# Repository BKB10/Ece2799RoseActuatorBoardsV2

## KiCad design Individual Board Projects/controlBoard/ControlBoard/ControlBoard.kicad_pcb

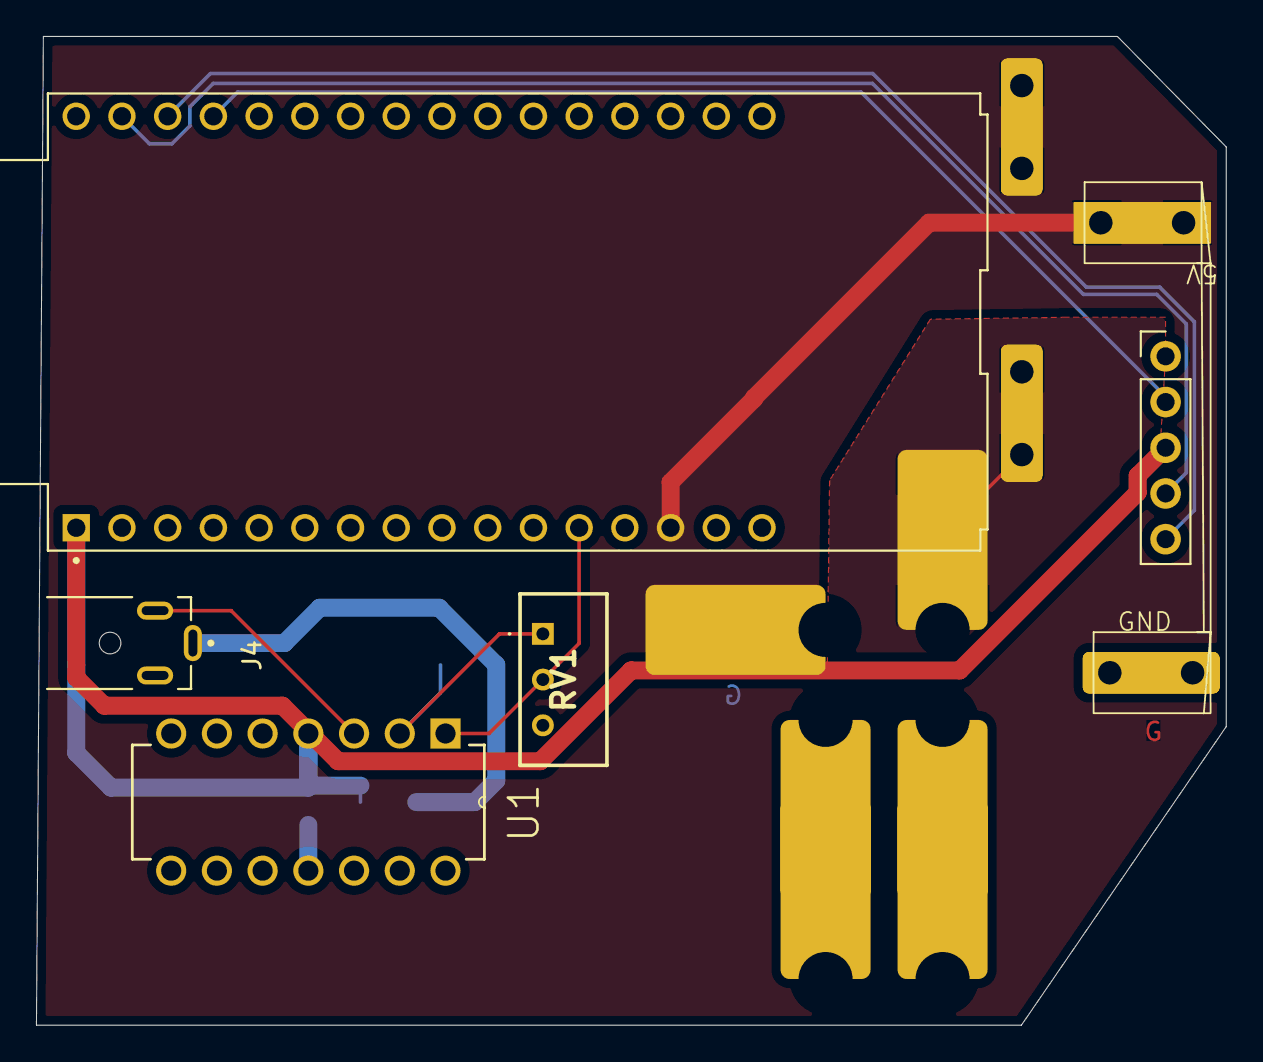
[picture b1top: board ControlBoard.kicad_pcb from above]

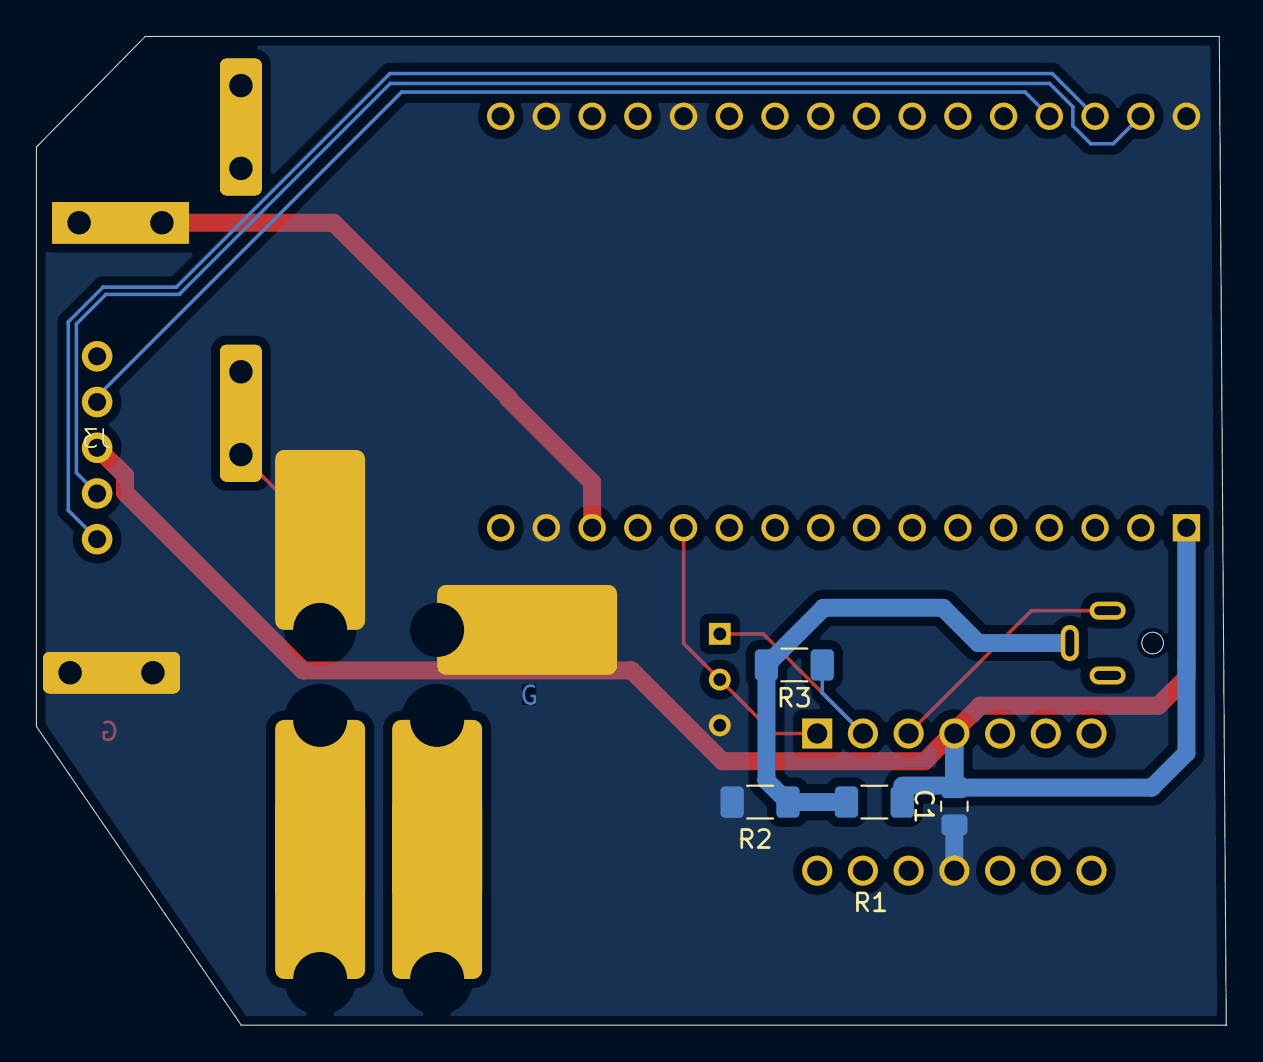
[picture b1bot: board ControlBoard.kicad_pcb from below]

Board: 2 copper layers, 66.1 x 54.9 mm, 12 parts (4 on the bottom side), 13 nets.

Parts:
B1: 12-24V -> 5V 20A; Buck-fourpins
C1: .1u; C_0805_2012Metric_Pad1.18x1.45mm_HandSolder
J1: USBCPD; USBC-PD-Module-twopins
J3: 5x2.54mm+2xBus; InterModuleConnectorMside
J4: MJ1-2503A; SAMESKY_MJ1-2503A
R1, R2: 40k; R_1206_3216Metric_Pad1.30x1.75mm_HandSolder
R3: 50; R_1206_3216Metric_Pad1.30x1.75mm_HandSolder
RV1: 1-400k; Potentiometer
U1: LMC6484IN_NOPB; DIP254P762X508-14
U2: 01000020Z
U3: ESP32-C6-DEVKITC-1-N8; MODULE_ESP32-C6-DEVKITC-1-N8

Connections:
+1.65V: J4.1, R1.2, R2.1, R3.2
+3.3V: C1.2, J3.4, R1.1, U1.4 (V+), U3.J1_1 (ESP_3V3)
+5V: J3.1, U2.2, U3.J1_14 (VCC_5V)
/ESP32_UART_RX: J3.6, U3.J3_3 (UART_RXD)
/ESP32_UART_TX: J3.5, U3.J3_2 (UART_TXD)
/To ESP32 ADC: RV1.2, U1.1 (OUT1), U3.J1_12 (GPIO2)
/USBC+: B1.1 (+Vin), J1.1
/USBC-: B1.2 (-Vin), J1.2
/nShoutRecive: J3.3, U3.J3_4 (GPIO15)
GND: B1.4 (-Vout), C1.1, J3.7, R2.2, RV1.3, U1.11 (V-), U3.J1_15 (GND_J1_15), U3.J3_1 (GND_J3_1), U3.J3_12 (GND_J3_12), U3.J3_15 (GND_J3_15)
unnamed: B1.3 (+Vout), U2.1
unnamed: R3.1, RV1.1, U1.2 (NEG1)
unnamed: J4.3, U1.3 (POS1)

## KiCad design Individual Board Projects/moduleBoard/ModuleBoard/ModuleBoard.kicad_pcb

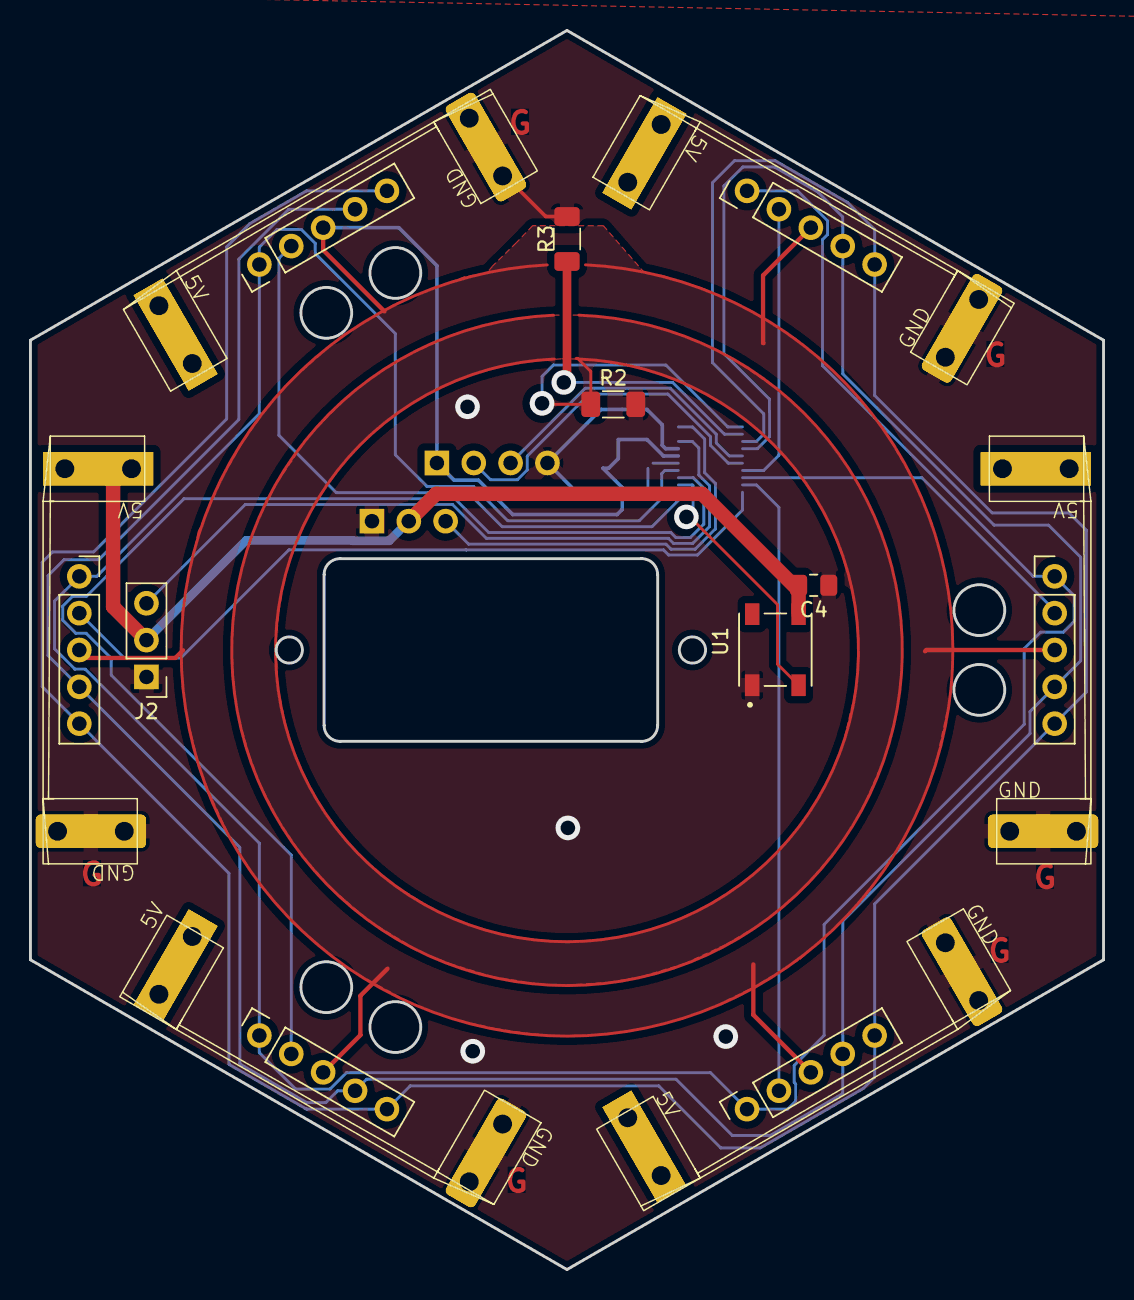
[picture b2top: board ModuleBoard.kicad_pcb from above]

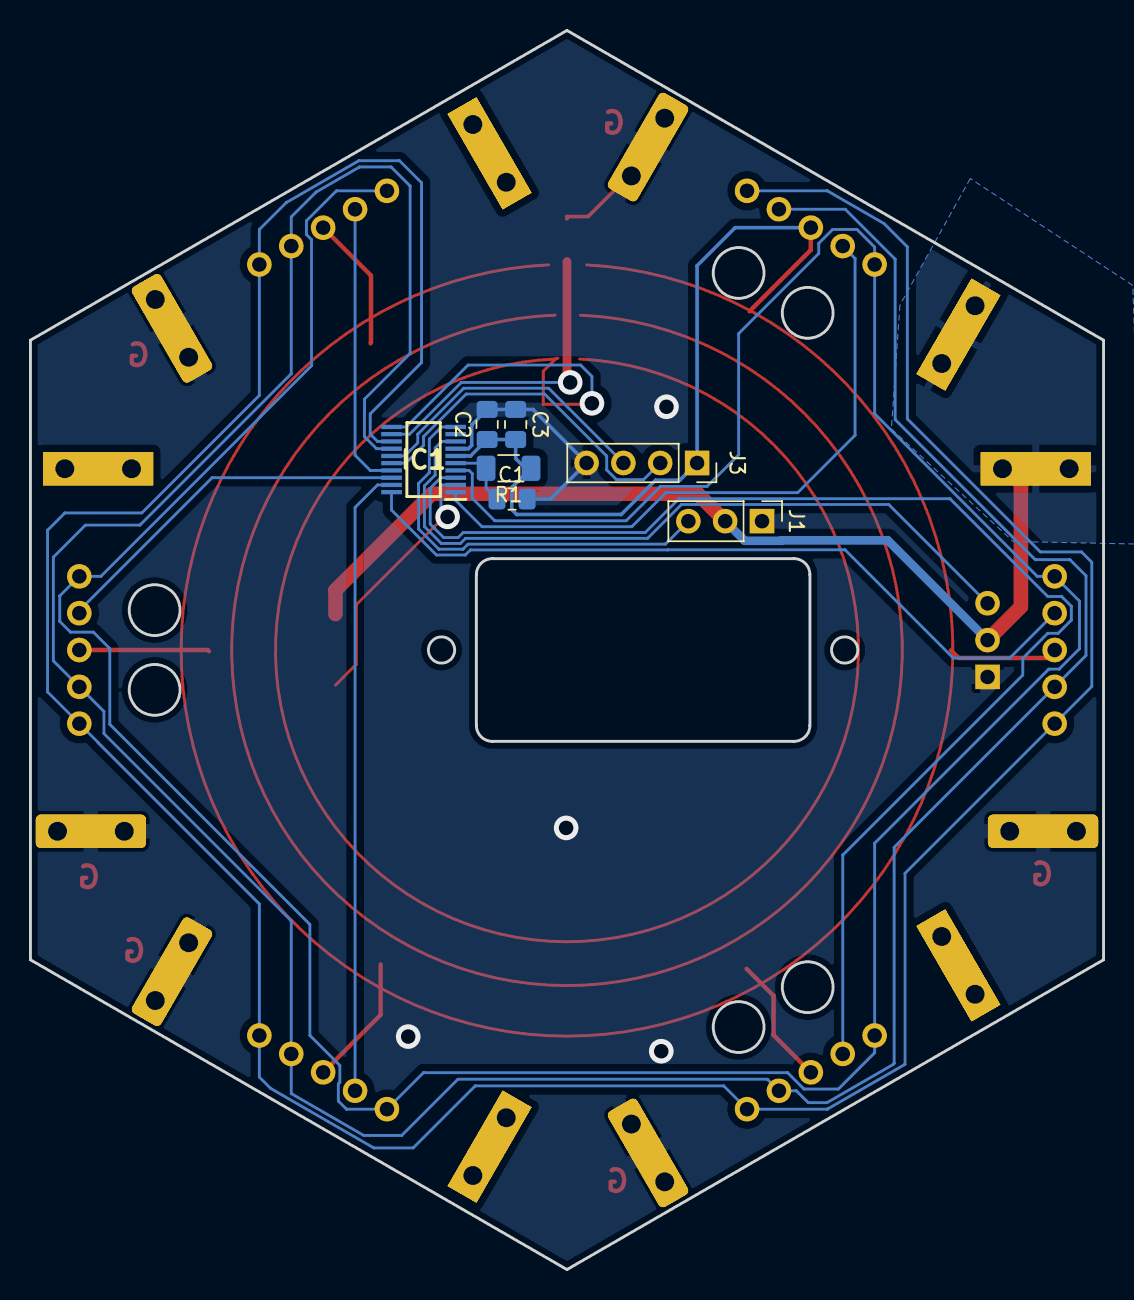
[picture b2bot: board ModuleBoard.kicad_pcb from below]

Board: 2 copper layers, 74.0 x 85.4 mm, 18 parts (7 on the bottom side), 20 nets.

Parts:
C1: 10n; C_0805_2012Metric_Pad1.18x1.45mm_HandSolder
C2: 10u; C_0805_2012Metric_Pad1.18x1.45mm_HandSolder
C3, C4: .1u; C_0805_2012Metric_Pad1.18x1.45mm_HandSolder
IC1: MSPM0C1103SDGS20R
J1: Rotation Servo; PinHeader_1x03_P2.54mm_Vertical
J2: Extention Servo; PinHeader_1x03_P2.54mm_Vertical
J3: Debug; PinSocket_1x04_P2.54mm_Vertical
J4, J5, J6, J7, J8, J9: 5x2.54mm+2xBus; InterModuleConnectorMside
R1: 47k; R_1206_3216Metric_Pad1.30x1.75mm_HandSolder
R2, R3: 40k; R_1206_3216Metric_Pad1.30x1.75mm_HandSolder
U1: FZ2812-5050; LED_FZ2812-5050

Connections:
+3.3V: C2.1, C3.2, IC1.6 (VDD), J3.1, J4.4, J5.4, J6.4, J7.4, J8.4, J9.4, R1.1
+5V: C4.2, J1.2, J2.2, J4.1, J5.1, J6.1, J7.1, J8.1, J9.1, U1.3 (VDD)
/Extention Bottom Out: IC1.11 (PA11), R2.1
/LED Sig: IC1.2 (PA27_/_A0), U1.2 (DIN)
/Linear Motor PWM: IC1.8 (PA2), J2.3
/MSP RX: IC1.14 (PA18_/_A7), J4.5, J5.5, J6.5, J7.5, J8.5, J9.5
/MSP TX: IC1.13 (PA17), J4.6, J5.6, J6.6, J7.6, J8.6, J9.6
/Rotary Motor PWM: IC1.10 (PA6), J1.3
/Rotation Key: IC1.12 (PA16_/_A8), R3.1
/SWCLK: IC1.16 (PA20_/_A6_/_SWCLK), J3.2
/SWDIO: IC1.15 (PA19_/_SWDIO), J3.3
/nShoutIn1: IC1.3 (PA28_/_A5), J4.3
/nShoutIn2: IC1.17 (PA22_/_A4), J7.3
/nShoutIn3: IC1.19 (PA24_/_A3), J5.3
/nShoutIn4: IC1.20 (PA25_/_A2), J8.3
/nShoutIn5: IC1.1 (PA26_/_A1), J6.3
/nShoutIn6: IC1.18 (PA23), J9.3
/nShoutOut: IC1.4 (PA0), J4.2, J5.2, J6.2, J7.2, J8.2, J9.2
GND: C1.2, C2.2, C3.1, C4.1, IC1.7 (VSS), J1.1, J2.1, J3.4, J4.7, J5.7, J6.7, J7.7, J8.7, J9.7, R2.2, R3.2, U1.1 (VSS)
unnamed: C1.1, IC1.5 (PA1_/_NRST), R1.2

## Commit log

2025-11-18 Fixed things, added microphone amplifier, ...
2025-11-18 Added footprint for MSPM0C1103SDGS20R
2025-11-20 Fixed amplifier resistors, fixed potentiometer
2025-11-21 schem Rev 1 Ready for layout
2025-11-24 Refrences Changed, Root file fixed, UART Note Added
2025-11-24 improved amplifier
2025-11-25 Direcctory reorganization footprints added
2025-11-25 gitignore update
2025-11-25 Sub Projects Created
2025-11-25 I am a master of design.
2025-12-01 Module Layout Rev 0
2025-12-01 Updated KiCad files
2025-12-02 Interconnect Board
2025-12-02 Updated ControlBoard design files
2025-12-02 module mods
2025-12-02 Better Layout Control Board
2025-12-02 Gerbers For Interconnect And Module
2025-12-02 Controll Finished - READY TO FAB
